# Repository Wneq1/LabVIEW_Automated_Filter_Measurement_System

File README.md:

# LabVIEW_Automated_Filter_Measurement_System

## 📋 Opis projektu
Projekt przedstawia system do zautomatyzowanego pomiaru charakterystyk częstotliwościowych filtrów aktywnych. Sercem układu jest autorska płytka PCB zaprojektowana w programie **KiCad**, zawierająca 6 różnych wariantów filtrów analogowych. System został stworzony z myślą o współpracy z aplikacją pomiarową w środowisku **LabVIEW**, co pozwala na automatyczne wykreślanie charakterystyk amplitodowo-fazowych.

## 🛠️ Architektura Sprzętowa (Hardware)

### 1. Sekcja Filtrów (Topologia Sallen-Key)
Na płytce znajduje się 6 filtrów aktywnych drugiego rzędu (2nd order). Wykorzystanie różnych wartości dobroci ($Q$) pozwala na demonstrację trzech klasycznych aproksymacji:

* **Bufory wejściowe (Wtórniki):** Zapewniają wysoką impedancję wejściową, eliminując wpływ impedancji źródła na parametry filtracji.
* **Filtry Dolnoprzepustowe (LPF) i Górnoprzepustowe (HPF):**
    * **$Q = 0.5$ (Bessel):** Filtr o najlepszej odpowiedzi impulsowej (brak przeregulowań) i liniowej fazie. Idealny do sygnałów prostokątnych i impulsowych.
    * **$Q = 0.707$ (Butterworth):** Filtr o maksymalnie płaskiej charakterystyce amplitudowej w paśmie przepustowym. Stanowi kompromis między szybkością opadania a odpowiedzią czasową.
    * **$Q = 2.0$ (Czebyszew):** Filtr o bardzo stromym zboczu opadania, ale kosztem pojawienia się pofalowań (ripple) i wzmocnienia w okolicy częstotliwości odcięcia.

Wybór konkretnej charakterystyki odbywa się poprzez przepięcie zworki na selektorze wyjściowym, co pozwala na natychmiastowe porównanie różnic w sygnale na oscyloskopie lub w programie LabVIEW.

### 2. Sekcja Filtrów Górnoprzepustowych (High-Pass)
Sekcja ta służy do tłumienia składowych o niskich częstotliwościach i przepuszczania sygnałów powyżej częstotliwości odcięcia ($f_c$). Zastosowano topologię Sallen-Key 2. rzędu, co pozwala na demonstrację wpływu dobroci ($Q$) na kształt "kolana" charakterystyki:

* **$Q = 0.5$ (Bessel )** 
* **$Q = 0.707$ (Butterworth)**
* **$Q = 2.0$ (Czebyszew)** 

### Porównanie parametrów konstrukcyjnych (HPF)
Wszystkie filtry oparte są na wzmacniaczu **OP07**, a różne typy odpowiedzi uzyskano poprzez precyzyjny dobór elementów biernych (zgodnie ze schematem):
* Kondensatory wejściowe (np. $C_{17}$, $C_{18}$) o wartości $10nF$.
* Rezystory ustalające dobroć (np. $R_{13} = 22k\Omega$, $R_{14} = 11k\Omega$).
### 3. Sekcja Zasilania (Power Supply)
Układ posiada zaawansowany blok zasilania, który umożliwia pracę z sygnałem zmiennym dzięki zasilaniu symetrycznemu:
* **Przetwornica DC-DC:** Użycie modułu **MGJ2D051515SC** pozwala na uzyskanie izolowanego napięcia symetrycznego $\pm 5V$  z pojedynczego wejścia DC.
* **Filtrowanie LC:** Zastosowanie dławika $L_1$ oraz kondensatorów $C_3$, $C_4$ minimalizuje tętnienia napięcia z przetwornicy impulsowej.
* **Zabezpieczenia:** Dioda chroniąca przed odwrotną polaryzacją oraz diody LED sygnalizujące obecność napięcia na szynach dodatniej i ujemnej.
* 

### 4. Schemat całego układu

## 🎨 Galeria Projektu i Wizualizacja PCB

W tej sekcji przedstawiono fizyczną strukturę projektu oraz finalny wygląd urządzenia po montażu. Projekt został zoptymalizowany pod kątem minimalizacji szumów oraz przejrzystości serwisowej.

### 1. Wizualizacja 3D (Render)
Dzięki narzędziom programu KiCad, wygenerowano realistyczny model 3D płytki **Active Filters Test Board**.
* **Layout:** Komponenty zostały rozmieszczone blokowo, co ułatwia diagnostykę sygnału od wejścia (Input) do wyjścia (Output).
* **Oznaczenia:** Na warstwie opisowej (silkscreen) umieszczono logotypy Politechniki Rzeszowskiej oraz KMiSD, a także czytelne etykiety dla zworek selekcyjnych dobroci $Q$.
* **Montaż:** Wykorzystano mieszaną technologię montażu (SMT dla układów scalonych i rezystorów, THT dla kondensatorów i złączy), co zapewnia kompromis między miniaturyzacją a łatwością modyfikacji.

### 2. Widok Warstwy Górnej (Top Layer)
Warstwa górna odpowiada głównie za prowadzenie sygnałów o wysokiej impedancji oraz zasilania wzmacniaczy operacyjnych:
* **Separacja Sygnałów:** Ścieżki sygnałowe są prowadzone w sposób możliwie najkrótszy, aby uniknąć zbierania zakłóceń elektromagnetycznych (EMI).
* **Blok Zasilania:** Wyraźnie wydzielona sekcja z przetwornicą **MGJ2D051515SC** i filtrem LC, która zasila całą płytkę napięciem symetrycznym $\pm 5V$.
* **Pola Masowe:** Wolne przestrzenie zostały wypełnione wylewką masy (Ground Plane), co poprawia stabilność pracy filtrów o wysokiej dobroci $Q=2.0$.

### 3. Widok Warstwy Dolnej (Bottom Layer)
Warstwa dolna pełni kluczową rolę w zapewnieniu integralności sygnałowej:
* **Ekranowanie:** Ciągła płaszczyzna masy na dolnej warstwie minimalizuje pętle masy i redukuje szumy przenoszone z sekcji zasilania impulsowego do czułych sekcji filtrów analogowych.
* **Przelotki (Vias):** Strategicznie rozmieszczone przelotki zapewniają niską impedancję połączeń między warstwami zasilania.

## 💻 Integracja z LabVIEW
W przyszłości projekt zostanie rozbudowy o automatyzacjie. Program w LabVIEW będzie obejmował:
1.  Sterowanie generatorem sygnałowym (częstotliwość sweep).
2.  Akwizycję danych przez kartę DAQ lub oscyloskop.
3.  Przetwarzanie danych i wizualizację charakterystyki amplitudowo-częstotliwościowej w czasie rzeczywistym.

## 🗂️ Struktura Repozytorium
* `/KiCad` - Pliki projektu PCB (schemat, layout, biblioteki).
* `/LabVIEW` - Pliki źródłowe programu pomiarowego (.vi).
* `/Documentation` - Dokumentacja techniczna i obliczenia filtrów.

---
*Projekt zrealizowany na Politechnice Rzeszowskiej (Katedra Metrologii i Systemów Diagnostycznych).*

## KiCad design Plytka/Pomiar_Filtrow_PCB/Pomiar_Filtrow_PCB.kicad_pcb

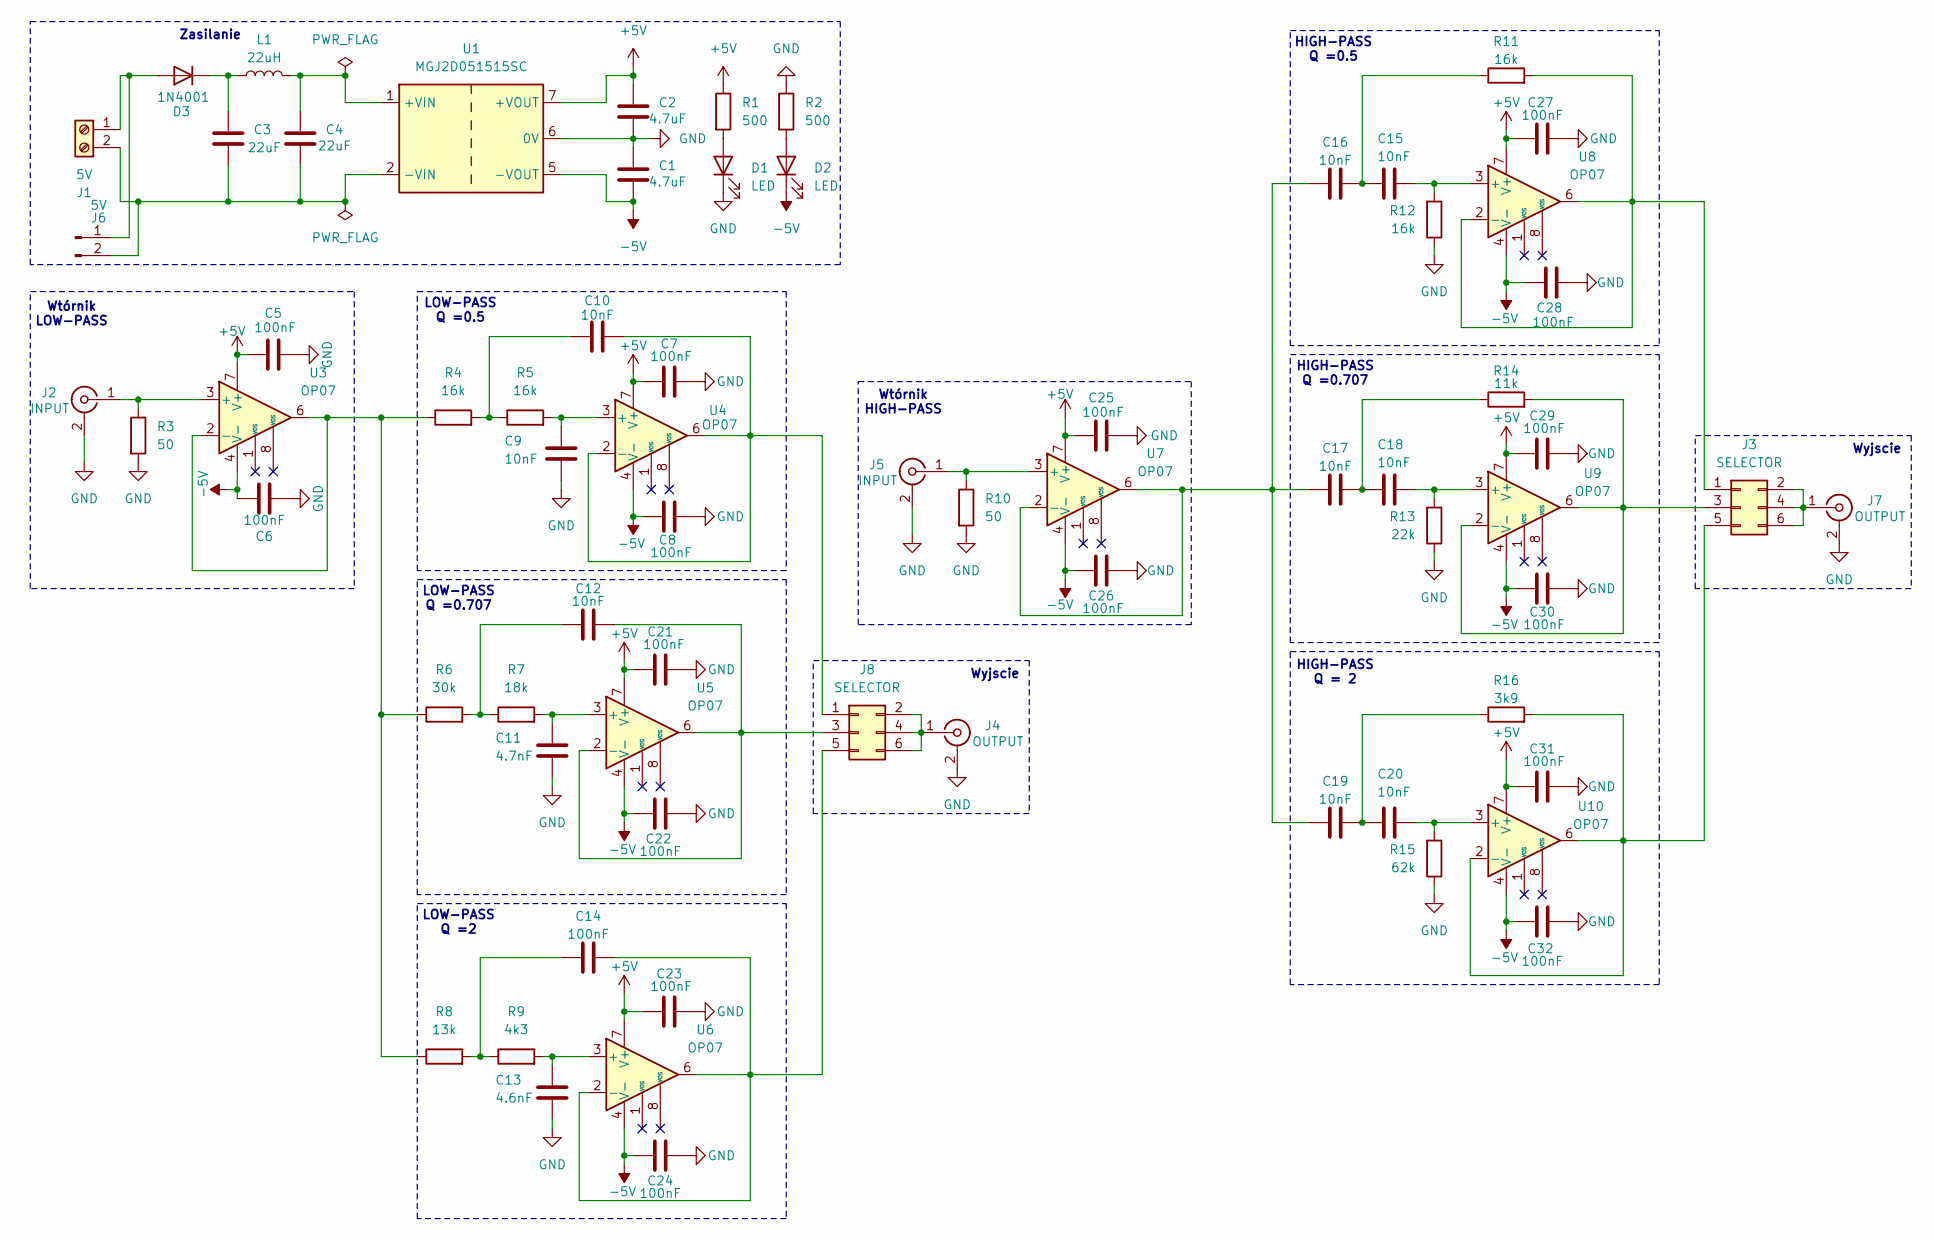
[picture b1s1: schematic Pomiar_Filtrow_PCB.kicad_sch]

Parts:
C1, C2: 4.7uF; C_Disc_D5.1mm_W3.2mm_P5.00mm
C3, C4: 22uF; C_Disc_D5.1mm_W3.2mm_P5.00mm
C5, C6, C7, C8, C14, C21, C22, C23, C24, C25, C26, C27, C28, C29, C30, C31, C32: 100nF; C_Disc_D5.1mm_W3.2mm_P5.00mm
C9, C10, C12, C15, C16, C17, C18, C19, C20: 10nF; C_Disc_D5.1mm_W3.2mm_P5.00mm
C11: 4.7nF; C_Disc_D5.1mm_W3.2mm_P5.00mm
C13: 4.6nF; C_Disc_D5.1mm_W3.2mm_P5.00mm
D1, D2: LED; LED_D3.0mm_FlatTop
D3: 1N4001; D_DO-41_SOD81_P10.16mm_Horizontal
J1: 5V; BarrelJack_GCT_DCJ200-10-A_Horizontal
J2, J5: INPUT; BNC_Amphenol_B6252HB-NPP3G-50_Horizontal
J3, J8: SELECTOR; PinHeader_2x03_P2.54mm_Vertical
J4, J7: OUTPUT; BNC_Amphenol_B6252HB-NPP3G-50_Horizontal
J6: 5V; PinHeader_1x02_P2.54mm_Vertical
L1: 22uH; L_Axial_L5.3mm_D2.2mm_P10.16mm_Horizontal_Vishay_IM-1
R1, R2: 500; R_1206_3216Metric_Pad1.30x1.75mm_HandSolder
R3, R10: 50; R_1206_3216Metric_Pad1.30x1.75mm_HandSolder
R4, R5, R11, R12: 16k; R_1206_3216Metric_Pad1.30x1.75mm_HandSolder
R6: 30k; R_1206_3216Metric_Pad1.30x1.75mm_HandSolder
R7: 18k; R_1206_3216Metric_Pad1.30x1.75mm_HandSolder
R8: 13k; R_1206_3216Metric_Pad1.30x1.75mm_HandSolder
R9: 4k3; R_1206_3216Metric_Pad1.30x1.75mm_HandSolder
R13: 22k; R_1206_3216Metric_Pad1.30x1.75mm_HandSolder
R14: 11k; R_1206_3216Metric_Pad1.30x1.75mm_HandSolder
R15: 62k; R_1206_3216Metric_Pad1.30x1.75mm_HandSolder
R16: 3k9; R_1206_3216Metric_Pad1.30x1.75mm_HandSolder
U1: MGJ2D051515SC; Converter_DCDC_Murata_MGJ2DxxxxxxSC_THT
U3, U4, U5, U6, U7, U8, U9, U10: OP07; SO-8_5.3x6.2mm_P1.27mm

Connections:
+5V: C2.2, C5.2, C7.2, C21.2, C23.2, C25.2, C27.2, C29.2, C31.2, R1.1, U1.7 (+VOUT), U3.7 (V+), U4.7 (V+), U5.7 (V+), U6.7 (V+), U7.7 (V+), U8.7 (V+), U9.7 (V+), U10.7 (V+)
-5V: C1.1, C6.2, C8.2, C22.2, C24.2, C26.2, C28.2, C30.2, C32.2, D2.1 (K), U1.5 (-VOUT), U3.4 (V-), U4.4 (V-), U5.4 (V-), U6.4 (V-), U7.4 (V-), U8.4 (V-), U9.4 (V-), U10.4 (V-)
GND: C1.2, C2.1, C5.1, C6.1, C7.1, C8.1, C9.2, C11.2, C13.2, C21.1, C22.1, C23.1, C24.1, C25.1, C26.1, C27.1, C28.1, C29.1, C30.1, C31.1, C32.1, D1.1 (K), J2.2 (Ext), J4.2 (Ext), J5.2 (Ext), J7.2 (Ext), R2.1, R3.2, R10.2, R12.1, R13.1, R15.1, U1.6 (0V)
unnamed: C10.1, R4.2, R5.1
unnamed: C12.1, R6.2, R7.1
unnamed: C14.1, R8.2, R9.1
unnamed: C15.2, C16.2, R11.1
unnamed: C17.2, C18.2, R14.1
unnamed: C19.2, C20.2, R16.1
unnamed: D1.2 (A), R1.2
unnamed: D2.2 (A), R2.2
unnamed: D3.2 (A), J1.1, J6.1
unnamed: C3.2, D3.1 (K), L1.1
unnamed: C3.1, C4.1, J1.2, J6.2, U1.2 (-VIN)
unnamed: J2.1 (In), R3.1, U3.3 (+)
unnamed: J3.1, R11.2, U8.2 (-), U8.6
unnamed: J3.2, J3.4, J3.6, J7.1 (In)
unnamed: J3.3, R14.2, U9.2 (-), U9.6
unnamed: J3.5, R16.2, U10.2 (-), U10.6
unnamed: J4.1 (In), J8.2, J8.4, J8.6
unnamed: J5.1 (In), R10.1, U7.3 (+)
unnamed: C10.2, J8.1, U4.2 (-), U4.6
unnamed: C12.2, J8.3, U5.2 (-), U5.6
unnamed: C14.2, J8.5, U6.2 (-), U6.6
unnamed: C4.2, L1.2, U1.1 (+VIN)
unnamed: R4.1, R6.1, R8.1, U3.2 (-), U3.6
unnamed: C9.1, R5.2, U4.3 (+)
unnamed: C11.1, R7.2, U5.3 (+)
unnamed: C13.1, R9.2, U6.3 (+)
unnamed: C16.1, C17.1, C19.1, U7.2 (-), U7.6
unnamed: C15.1, R12.2, U8.3 (+)
unnamed: C18.1, R13.2, U9.3 (+)
unnamed: C20.1, R15.2, U10.3 (+)

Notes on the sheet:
Wyjscie
LOW-PASS Q =2
LOW-PASS Q =0.707
Zasilanie
Wtórnik HIGH-PASS
HIGH-PASS Q =0.5
HIGH-PASS Q = 2
HIGH-PASS Q =0.707
LOW-PASS Q =0.5
Wtórnik LOW-PASS

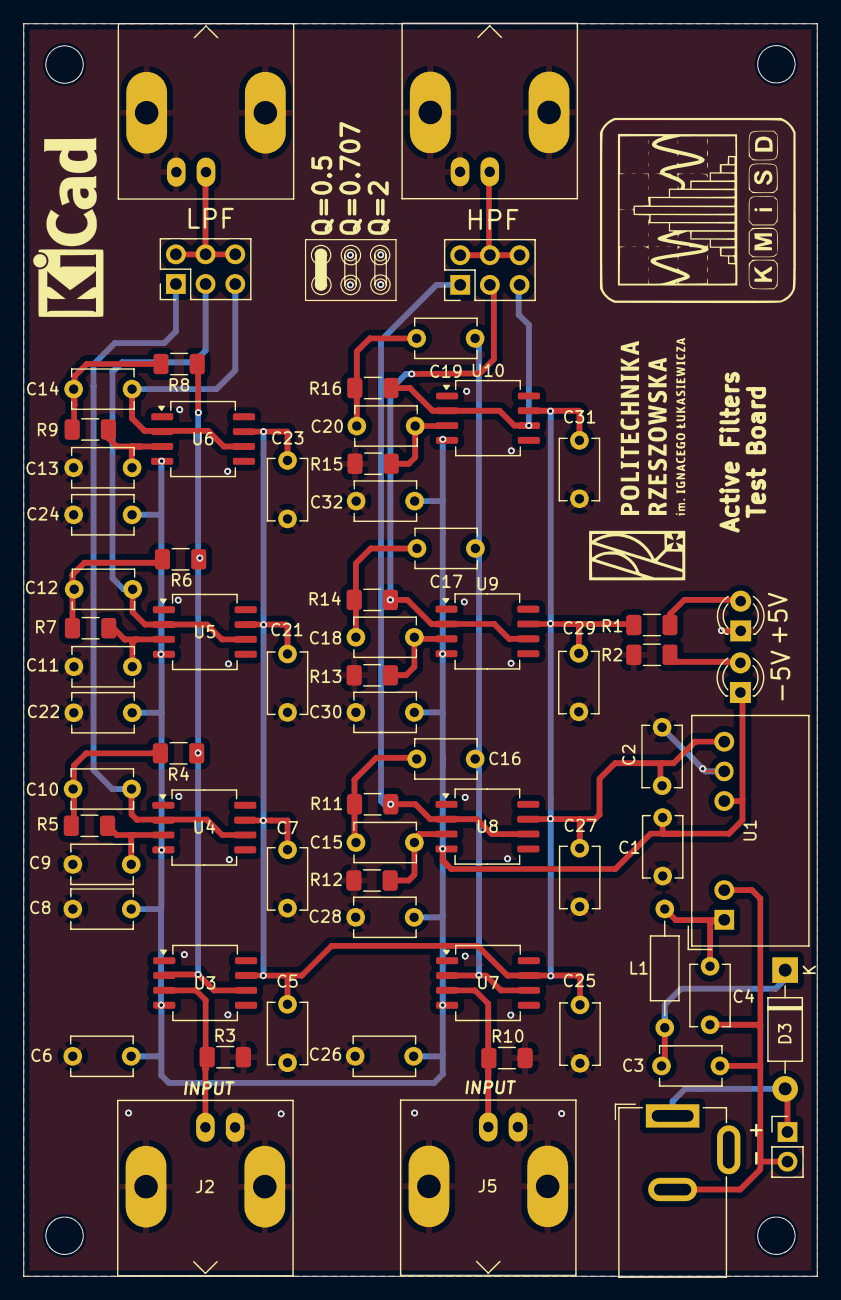
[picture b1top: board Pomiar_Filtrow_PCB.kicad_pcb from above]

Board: 2 copper layers, 67.9 x 107.2 mm, 69 parts (0 on the bottom side), 33 nets.

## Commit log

2025-11-14 Create PCB
2025-11-14 Add images to README for project visualization
    Added multiple images to enhance project documentation.
2025-11-14 Update images in README.md
    Replaced two images in the README with new ones.
2026-01-16 Clarify project description in README.md
    Updated project description to clarify the system's capabilities.
2026-01-16 Enhance README with filter and power supply details
    Added detailed descriptions for filter sections and power supply in the README.
2026-01-16 Clean up README by removing duplicate content
    Removed duplicate images and unnecessary text from the README.
2026-01-16 Update README with images and additional details
    Added images and enhanced descriptions for various sections.
2026-01-16 Revise LabVIEW integration project description
    Updated the description of the LabVIEW integration section to reflect future enhancements.
